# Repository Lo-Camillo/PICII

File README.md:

# Porta Medicamentos Inteligente
#### Grupo: Aryelle Siqueira, Giselle Pereira e Lohayne Camillo

Muitas pessoas enfrentam dificuldade  para lembrar de tomar seus medicamentos corretamente, especialmente quando têm que tomar múltiplos remédios diariamente.

O porta medicamentos inteligente surge como uma solução para ajudar a superar esses desafios.

## Como funciona?

O porta medicamentos possui 5 compartimentos para armazenar comprimidos. Através de um aplicativo, o usuário pode programar horários específicos para cada remédio, definindo qual compartimento será aberto.

O porta comprimidos possui um modo de programação no qual, ao selecionar um botão, o Wi-Fi será ativado para buscar diretamente do servidor os horários programados no aplicativo.

No horário programado, um alarme tocará, e ao pressionar um botão, o compartimento designado será aberto. Um visor mostrará a quantidade de comprimidos a serem ingeridos. Ao final da ingestão, ao pressionar o botão novamente, o compartimento girará para a próxima posição se houver outro remédio a ser tomado, caso contrário, retornará à posição inicial.

## Software

- [Código fonte e documentação do aplicativo](https://github.com/giselle-lab/porta-comprimidos).

- [Código fonte e documentação da API](https://github.com/AryelleSiqueira/pillbox-api.git).

- [Código fonte e documentação da ESP8266](https://github.com/AryelleSiqueira/porta-medicamentos-esp8266.git).

## Hardware

- [Documentação do hardware do projeto](Hardware_doc).

## Fotos & Vídeos

- [Acessar pasta de fotos e vídeos do projeto](Fotos&Videos).

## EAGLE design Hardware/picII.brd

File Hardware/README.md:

# Hardware

Para o hardware deste projeto, foi desenvolvida uma placa de circuito impresso em cobre para acomodar os componentes.

## Componentes

Os seguintes componentes foram usados:

- ESP8266 NodeMCU
- Motor de Passo 28BYJ-48 com Driver ULN2003
- Display OLED 0.96″ I2C - 128×64
- L7805C Regulador de Tensão 5V
- Push Button
- 3 resistores de 10k
- Buzzer
- Sockets
- Bateria 9V
- Placa de cobre

## Projeto no Eagle

A imagem a seguir demonstra o esquemático desenvolvido no software Eagle para confecção da placa. 

Esta próxima imagem mostra o arquivo Board, onde mostra os componentes em seus respectivos lugares na placa:

Alguns detalhes importantes a serem destacados:

- Na caixa desenvolvida, os botões e o visor estão posicionados voltados para fora, o que exigiu que eles fizessem parte de uma placa separada. Portanto, no esquemático, foram inseridos separadores onde, por meio de jumpers, as trilhas poderiam ser conectadas para interligar essas placas. O mesmo conceito se aplica aos conectores do motor.

## Caixa

Para o projeto, foi criada uma caixa em MDF. Na figura a seguir, podemos observar a estrutura dessa caixa.

Com o objetivo de acomodar os comprimidos, a parte superior foi dividida em 6 compartimentos, com um deles sempre permanecendo aberto, considerado como a posição inicial do motor.

A parte inferior abriga a placa de circuito impresso desenvolvida, que contém os componentes, bem como os botões e o display estão afixados nessa região.

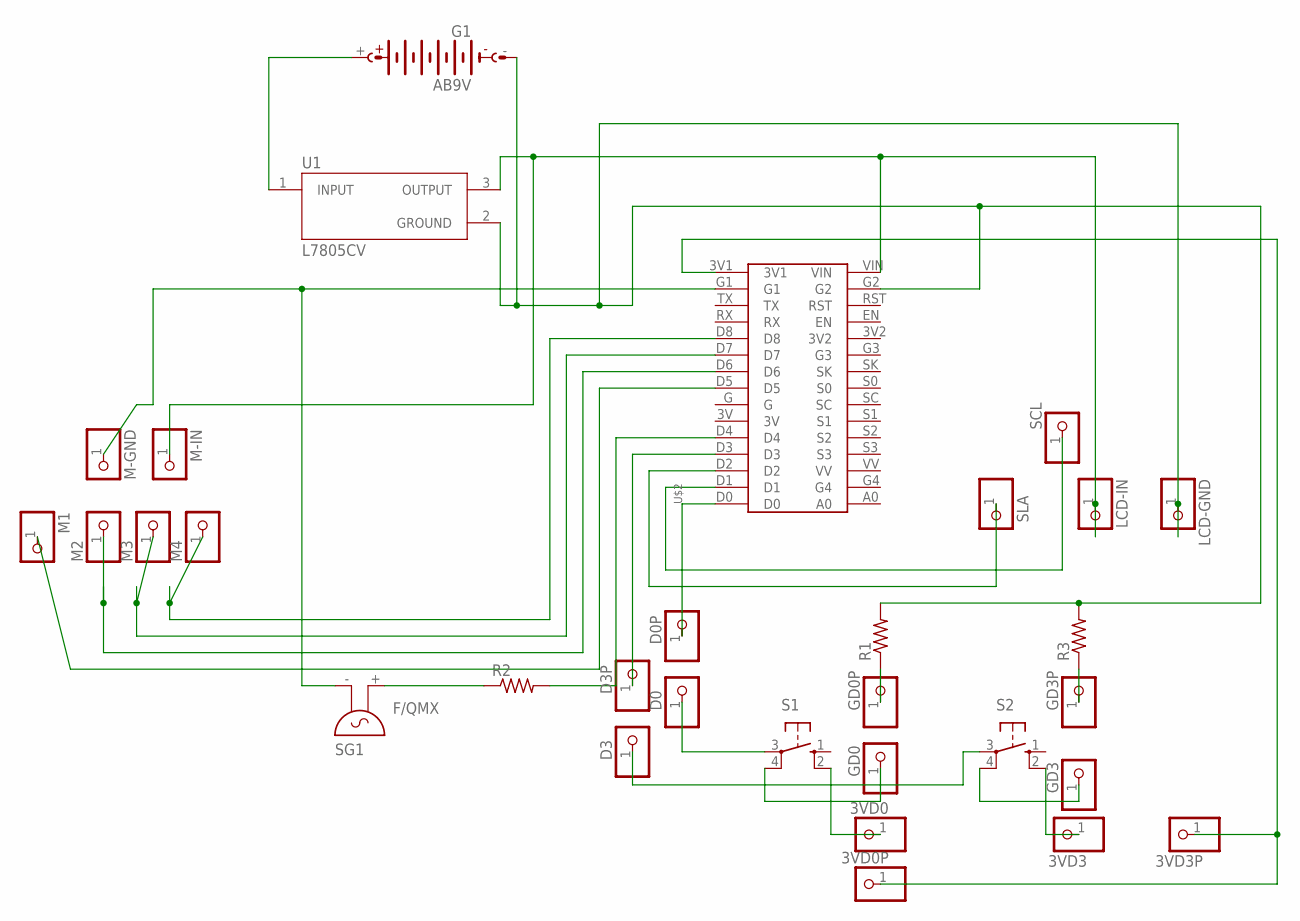
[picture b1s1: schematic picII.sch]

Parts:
3VD0, 3VD0P, 3VD3, 3VD3P: PINHD-1X1; 1X01
D0, D0P, D3, D3P: PINHD-1X1; 1X01
G1: AB9V
GD0, GD0P, GD3, GD3P: PINHD-1X1; 1X01
LCD-GND: PINHD-1X1; 1X01
LCD-IN: PINHD-1X1; 1X01
M1, M2, M3, M4: PINHD-1X1; 1X01
M-GND: PINHD-1X1; 1X01
M-IN: PINHD-1X1; 1X01
R1, R2, R3: R-US_0204/7; 0204/7
S1, S2: 40-XX; B3F-40XX
SCL: PINHD-1X1; 1X01
SG1: F/QMX
SLA: PINHD-1X1; 1X01
U1: L7805CV; TO255P1040X460X1968-3
U$2: LOLIN

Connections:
unnamed: G1.+, U1.1 (INPUT)
unnamed: R2.1, SG1.+ (2)
unnamed: 3VD0P.1, 3VD3P.1, U$2.3V1
unnamed: M1.1, U$2.D5
unnamed: M2.1, U$2.D6
unnamed: R2.2, U$2.D4
unnamed: GD0.1, S1.4 (P1)
unnamed: SLA.1, U$2.D2
unnamed: SCL.1, U$2.D1
unnamed: M3.1, U$2.D7
unnamed: M4.1, U$2.D8
unnamed: D0.1, S1.3
unnamed: D3.1, S2.3
unnamed: M-GND.1, SG1.- (1), U$2.G1
unnamed: G1.-, LCD-GND.1, R1.2, R3.2, U1.2 (GROUND), U$2.G2
unnamed: GD3.1, S2.4 (P1)
unnamed: LCD-IN.1, M-IN.1, U1.3 (OUTPUT), U$2.VIN
unnamed: GD0P.1, R1.1
unnamed: GD3P.1, R3.1
unnamed: 3VD0.1, S1.2 (S1)
unnamed: 3VD3.1, S2.2 (S1)
unnamed: D0P.1, U$2.D0
unnamed: D3P.1, U$2.D3

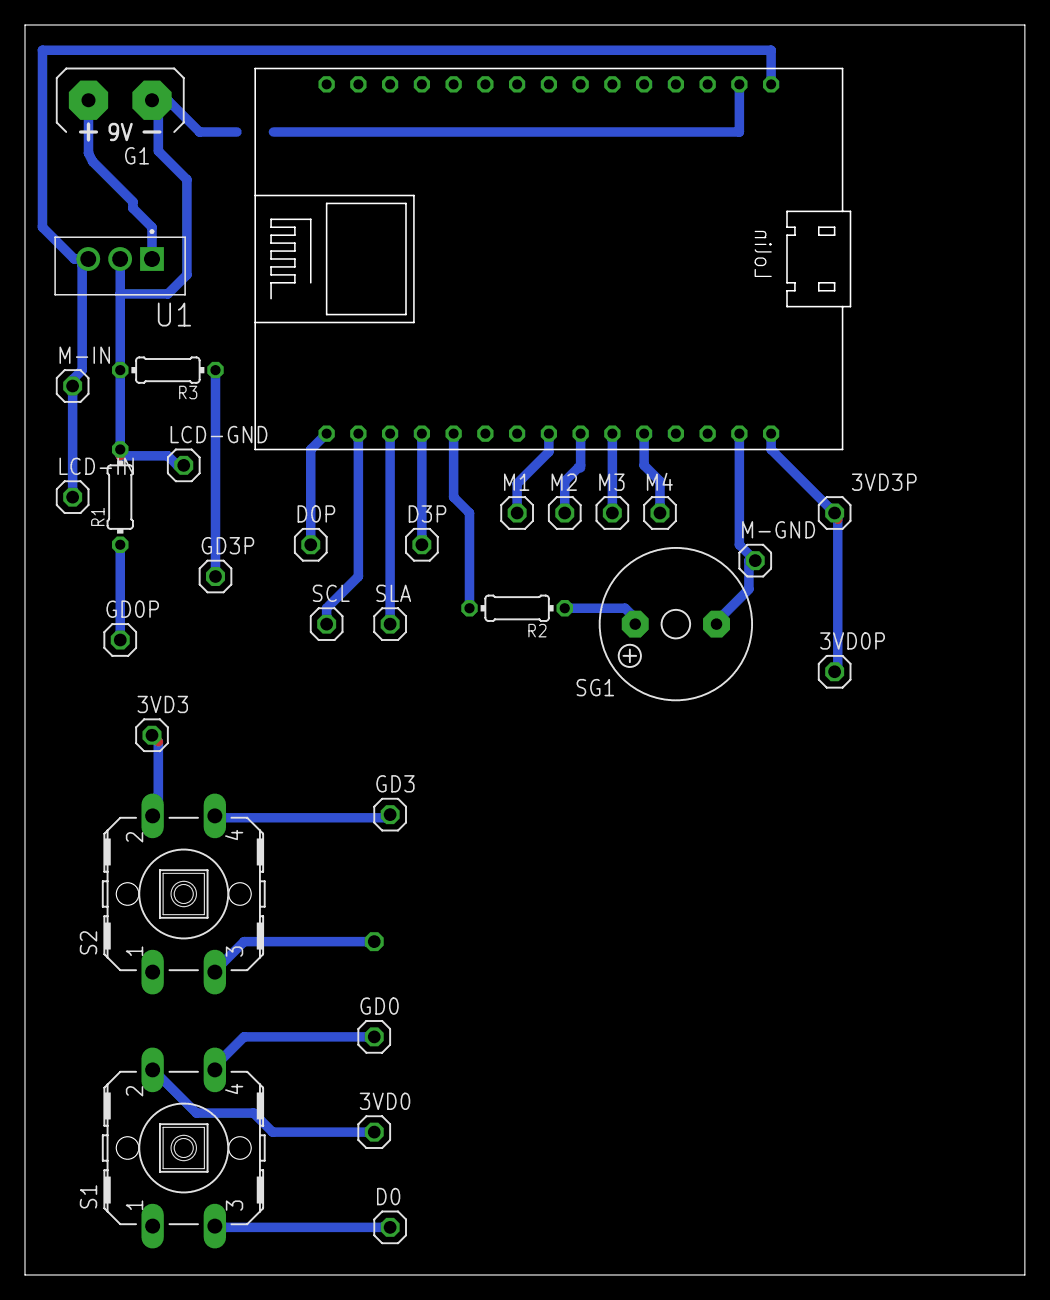
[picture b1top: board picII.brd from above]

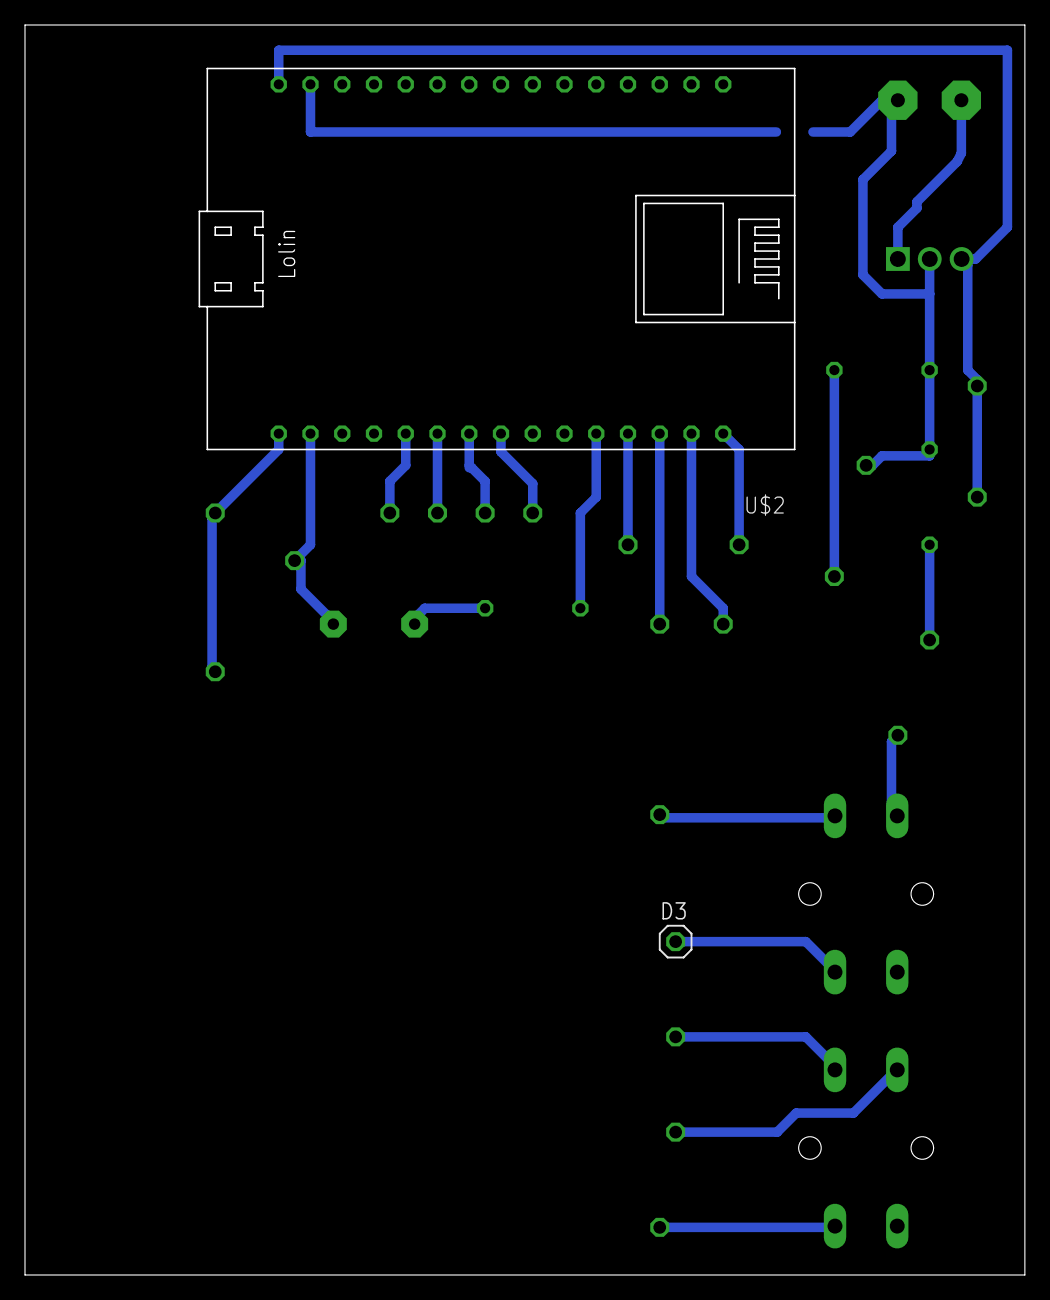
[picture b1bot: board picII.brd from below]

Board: 2 copper layers, 80.0 x 100.0 mm, 31 parts (2 on the bottom side), 23 nets.

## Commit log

2023-05-02 Pré Projeto
2023-07-23 relatorio
2023-07-23 rel.
2023-07-25 submodules
2023-07-25 app submodule
2023-07-25 submodules and readme updated
2023-07-26 api submodule
2023-07-26 Add photo and name of members
